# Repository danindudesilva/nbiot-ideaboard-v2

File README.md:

# Ideamart NB-IoT Ideaboard
###### version 2.0

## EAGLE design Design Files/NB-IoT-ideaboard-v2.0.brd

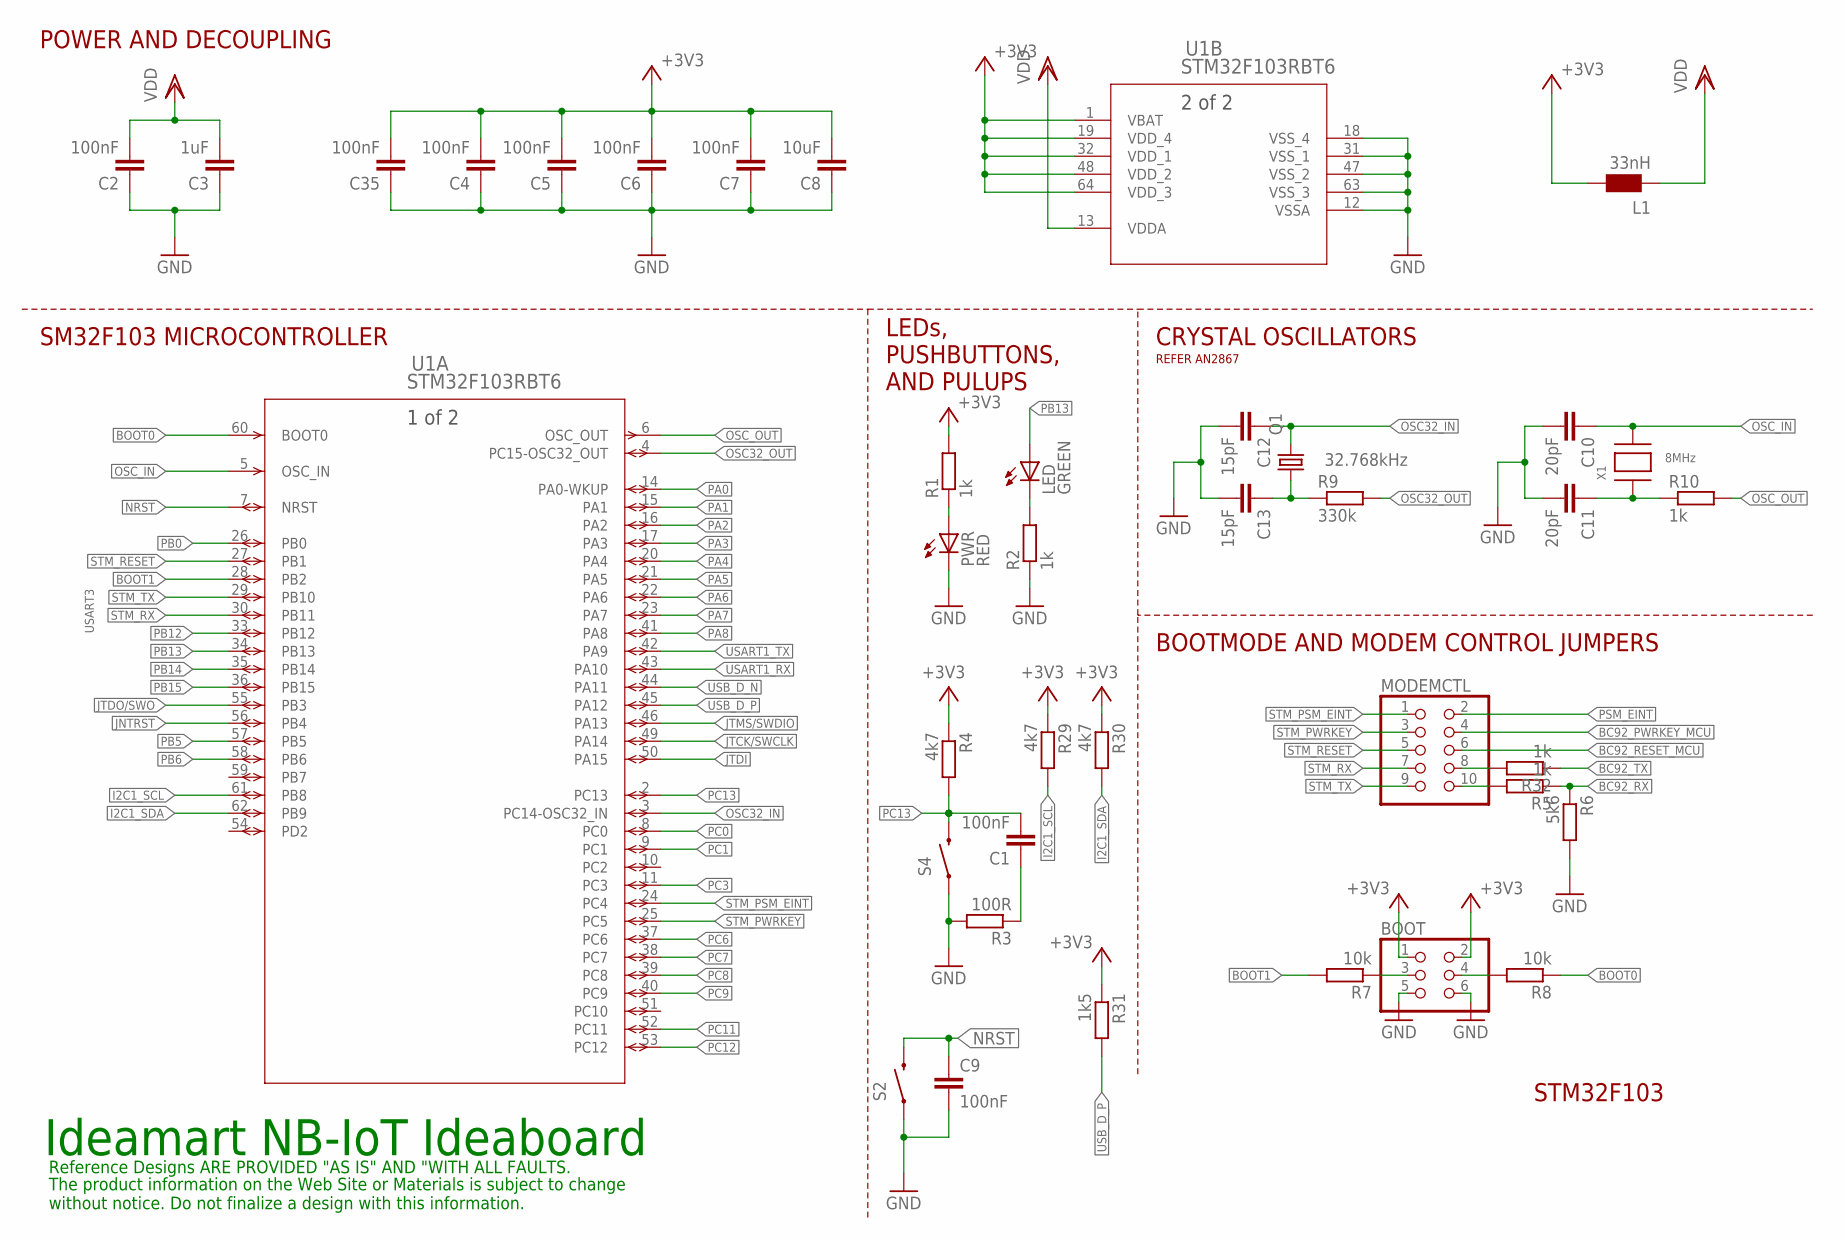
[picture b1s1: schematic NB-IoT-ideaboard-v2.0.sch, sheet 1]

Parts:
BOOT: PINHD-2X03_2.54; 2X03
C1, C2, C4, C5, C6, C7, C9, C35: 100nF; C0805
C3: 1uF; C0805
C8: 10uF; C1206
C10, C11: 20pF; C0805
C12, C13: 15pF; C0805
L1: 33nH; 0603
LED: GREEN; CHIP-LED0805
MODEMCTL: PINHD-2X05_2.54; 2X05
PWR: RED; CHIP-LED0805
Q1: 32.768kHz; 3.2X1.5
R1, R2, R5, R10, R32: 1k; R0805
R3: 100R; R0805
R4, R29, R30: 4k7; R0805
R6: 5k6; R0805
R7, R8: 10k; R0805
R9: 330k; R0805
R31: 1k5; R0805
S2, S4: SWITCH-MOMENTARY-2SMD; TACTILE-SWITCH-SMD
U1: STM32F103RBT6; LQFP64-10X10MM
X1: 8MHz; NX5032

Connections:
+3V3: BOOT.1, BOOT.2, C4.2, C5.2, C6.2, C7.2, C8.2, C35.2, L1.2, R1.2, R4.1, R29.1, R30.1, R31.1, U1.1 (VBAT), U1.19 (VDD_4), U1.32 (VDD_1), U1.48 (VDD_2), U1.64 (VDD_3); also elsewhere on the board
BC92_PWRKEY_MCU: MODEMCTL.4; also elsewhere on the board
BC92_RESET_MCU: MODEMCTL.6; also elsewhere on the board
BC92_RX: R5.1, R6.1; also elsewhere on the board
BC92_TX: R32.1; also elsewhere on the board
BOOT0: R8.1, U1.60 (BOOT0)
BOOT1: R7.2, U1.28 (PB2)
GND: BOOT.5, BOOT.6, C2.1, C3.1, C4.1, C5.1, C6.1, C7.1, C8.1, C9.2, C10.2, C11.2, C12.2, C13.2, C35.1, PWR.C, R2.1, R3.2, R6.2, S2.1, S4.1, U1.12 (VSSA), U1.18 (VSS_4), U1.31 (VSS_1), U1.47 (VSS_2), U1.63 (VSS_3); also elsewhere on the board
I2C1_SCL: R29.2, U1.61 (PB8); also elsewhere on the board
I2C1_SDA: R30.2, U1.62 (PB9); also elsewhere on the board
JNTRST: U1.56 (PB4); also elsewhere on the board
JTCK/SWCLK: U1.49 (PA14); also elsewhere on the board
JTDI: U1.50 (PA15)
JTDO/SWO: U1.55 (PB3); also elsewhere on the board
JTMS/SWDIO: U1.46 (PA13); also elsewhere on the board
unnamed: BOOT.3, R7.1
unnamed: PWR.A, R1.1
unnamed: C11.1, R10.1, X1.P$1
unnamed: C13.1, Q1.1, R9.1
unnamed: MODEMCTL.10, R5.2
unnamed: MODEMCTL.8, R32.2
unnamed: C1.1, R3.1
unnamed: BOOT.4, R8.2
unnamed: LED.C, R2.2
NRST: C9.1, S2.3 (2), U1.7 (NRST); also elsewhere on the board
OSC32_IN: C12.1, Q1.2, U1.3 (PC14-OSC32_IN)
OSC32_OUT: R9.2, U1.4 (PC15-OSC32_OUT)
OSC_IN: C10.1, U1.5 (OSC_IN), X1.P$2
OSC_OUT: R10.2, U1.6 (OSC_OUT)
PA0: U1.14 (PA0-WKUP); also elsewhere on the board
PA1: U1.15 (PA1); also elsewhere on the board
PA2: U1.16 (PA2); also elsewhere on the board
PA3: U1.17 (PA3); also elsewhere on the board
PA4: U1.20 (PA4); also elsewhere on the board
PA5: U1.21 (PA5); also elsewhere on the board
PA6: U1.22 (PA6); also elsewhere on the board
PA7: U1.23 (PA7); also elsewhere on the board
PA8: U1.41 (PA8); also elsewhere on the board
PB0: U1.26 (PB0); also elsewhere on the board
PB5: U1.57 (PB5); also elsewhere on the board
PB6: U1.58 (PB6); also elsewhere on the board
PB12: U1.33 (PB12); also elsewhere on the board
PB13: LED.A, U1.34 (PB13); also elsewhere on the board
PB14: U1.35 (PB14); also elsewhere on the board
PB15: U1.36 (PB15); also elsewhere on the board
PC0: U1.8 (PC0); also elsewhere on the board
PC1: U1.9 (PC1); also elsewhere on the board
PC3: U1.11 (PC3); also elsewhere on the board
PC6: U1.37 (PC6); also elsewhere on the board
PC7: U1.38 (PC7); also elsewhere on the board
PC8: U1.39 (PC8); also elsewhere on the board
PC9: U1.40 (PC9); also elsewhere on the board
PC11: U1.52 (PC11); also elsewhere on the board
PC12: U1.53 (PC12); also elsewhere on the board
PC13: C1.2, R4.2, S4.3 (2), U1.2 (PC13)
PSM_EINT: MODEMCTL.2; also elsewhere on the board
STM_PSM_EINT: MODEMCTL.1, U1.24 (PC4)
STM_PWRKEY: MODEMCTL.3, U1.25 (PC5)
STM_RESET: MODEMCTL.5, U1.27 (PB1)
STM_RX: MODEMCTL.7, U1.30 (PB11)
STM_TX: MODEMCTL.9, U1.29 (PB10)
USART1_RX: U1.43 (PA10); also elsewhere on the board
USART1_TX: U1.42 (PA9); also elsewhere on the board
USB_D_N: U1.44 (PA11); also elsewhere on the board
USB_D_P: R31.2, U1.45 (PA12); also elsewhere on the board
VDD: C2.2, C3.2, L1.1, U1.13 (VDDA)

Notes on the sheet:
Ideamart NB-IoT Ideaboard
Reference Designs ARE PROVIDED "AS IS" AND "WITH ALL FAULTS.
The product information on the Web Site or Materials is subject to change without notice. Do not finalize a design with this information.
USART3
POWER AND DECOUPLING
SM32F103 MICROCONTROLLER
BOOTMODE AND MODEM CONTROL JUMPERS
CRYSTAL OSCILLATORS
LEDs, PUSHBUTTONS, AND PULUPS
STM32F103
REFER AN2867

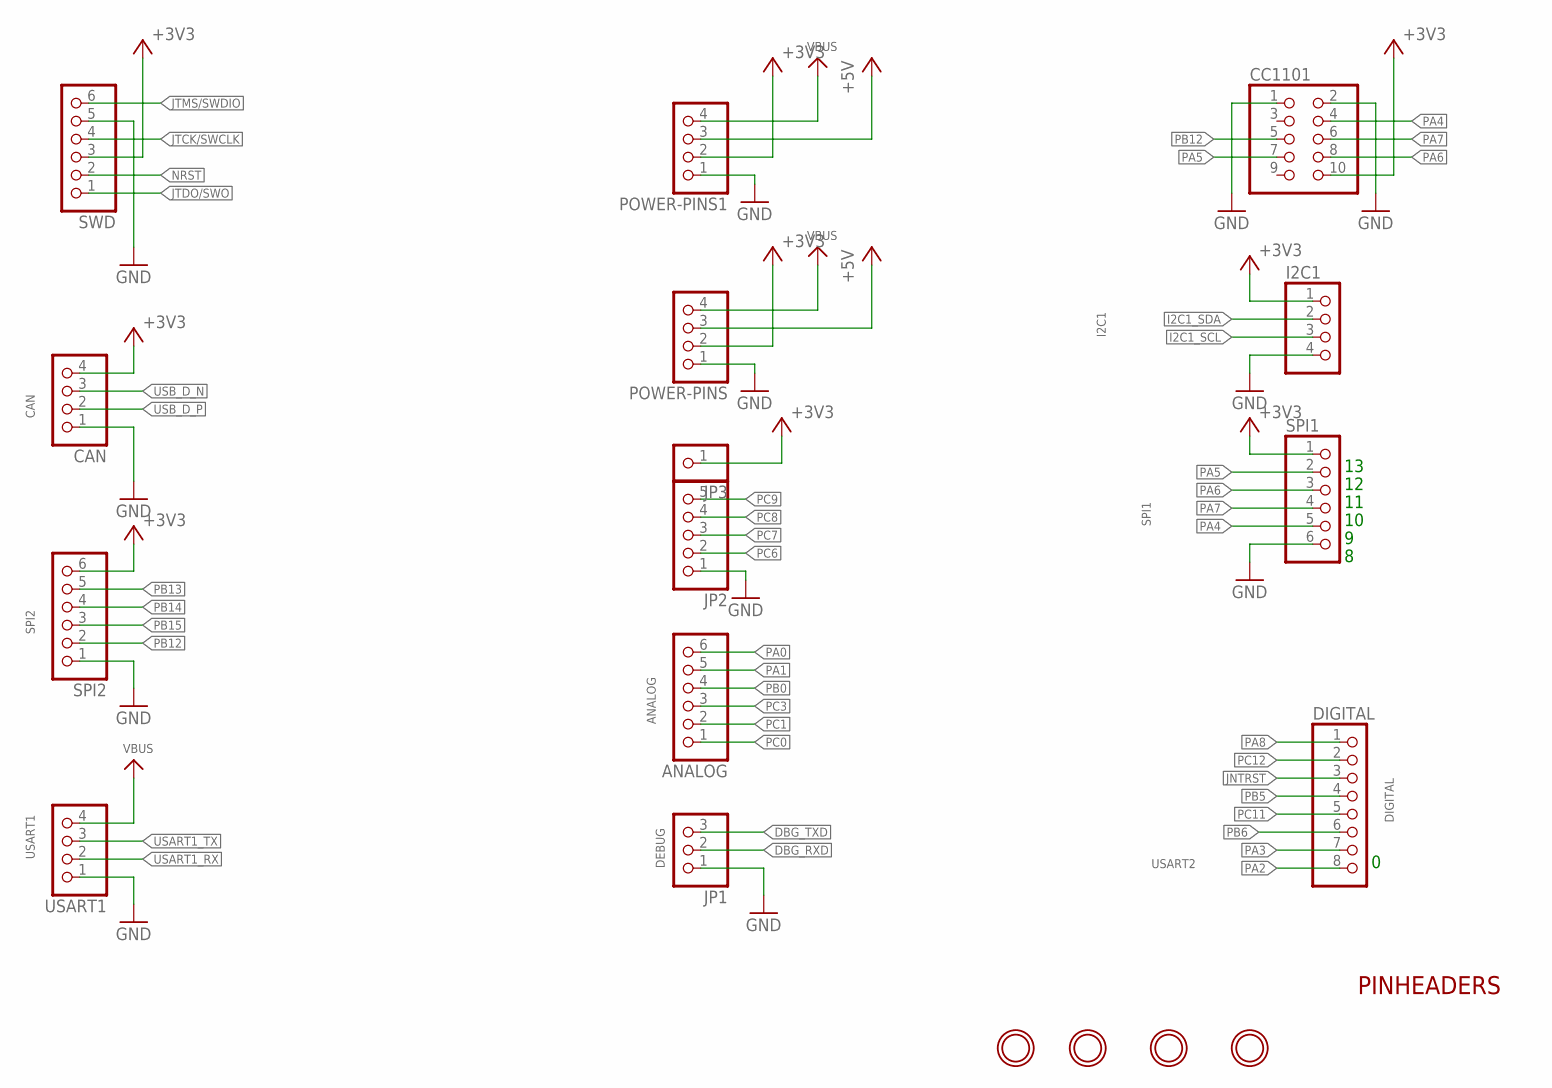
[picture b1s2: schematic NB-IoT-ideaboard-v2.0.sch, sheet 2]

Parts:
$H1, $H2, $H3, $H4: MOUNTINGHOLE3.0THIN; MOUNTINGHOLE_3.0_PLATEDTHIN
ANALOG: PINHD-1X06_2.54-S; 1X06-S
CAN: PINHD-1X04_2.54-S; 1X04-S
CC1101: PINHD-2X05_2.54; 2X05
DIGITAL: PINHD-1X08_2.54-S; 1X08-S
I2C1: PINHD-1X04_2.54-S; 1X04-S
JP1: PINHD-1X03_2.54-S; 1X03-S
JP2: PINHD-1X05_2.54-S; 1X05-S
JP3: PINHD-1X01_2.54-S; 1X01-S
POWER-PINS, POWER-PINS1: PINHD-1X04_2.54-S; 1X04-S
SPI1, SPI2: PINHD-1X06_2.54-S; 1X06-S
SWD: PINHD-1X06_2.54-S; 1X06-S
USART1: PINHD-1X04_2.54-S; 1X04-S

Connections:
+3V3: CAN.4, CC1101.10, I2C1.1, JP3.1, POWER-PINS.2, POWER-PINS1.2, SPI1.1, SPI2.6, SWD.3; also elsewhere on the board
+5V: POWER-PINS.3, POWER-PINS1.3; also elsewhere on the board
DBG_RXD: JP1.2; also elsewhere on the board
DBG_TXD: JP1.3; also elsewhere on the board
GND: CAN.1, CC1101.1, CC1101.2, I2C1.4, JP1.1, JP2.1, POWER-PINS.1, POWER-PINS1.1, SPI1.6, SPI2.1, SWD.5, USART1.1; also elsewhere on the board
I2C1_SCL: I2C1.3; also elsewhere on the board
I2C1_SDA: I2C1.2; also elsewhere on the board
JNTRST: DIGITAL.3; also elsewhere on the board
JTCK/SWCLK: SWD.4; also elsewhere on the board
JTDO/SWO: SWD.1; also elsewhere on the board
JTMS/SWDIO: SWD.6; also elsewhere on the board
NRST: SWD.2; also elsewhere on the board
PA0: ANALOG.6; also elsewhere on the board
PA1: ANALOG.5; also elsewhere on the board
PA2: DIGITAL.8; also elsewhere on the board
PA3: DIGITAL.7; also elsewhere on the board
PA4: CC1101.4, SPI1.5; also elsewhere on the board
PA5: CC1101.7, SPI1.2; also elsewhere on the board
PA6: CC1101.8, SPI1.3; also elsewhere on the board
PA7: CC1101.6, SPI1.4; also elsewhere on the board
PA8: DIGITAL.1; also elsewhere on the board
PB0: ANALOG.4; also elsewhere on the board
PB5: DIGITAL.4; also elsewhere on the board
PB6: DIGITAL.6; also elsewhere on the board
PB12: CC1101.5, SPI2.2; also elsewhere on the board
PB13: SPI2.5; also elsewhere on the board
PB14: SPI2.4; also elsewhere on the board
PB15: SPI2.3; also elsewhere on the board
PC0: ANALOG.1; also elsewhere on the board
PC1: ANALOG.2; also elsewhere on the board
PC3: ANALOG.3; also elsewhere on the board
PC6: JP2.2; also elsewhere on the board
PC7: JP2.3; also elsewhere on the board
PC8: JP2.4; also elsewhere on the board
PC9: JP2.5; also elsewhere on the board
PC11: DIGITAL.5; also elsewhere on the board
PC12: DIGITAL.2; also elsewhere on the board
USART1_RX: USART1.2; also elsewhere on the board
USART1_TX: USART1.3; also elsewhere on the board
USB_D_N: CAN.3; also elsewhere on the board
USB_D_P: CAN.2; also elsewhere on the board
VBUS: POWER-PINS.4, POWER-PINS1.4, USART1.4; also elsewhere on the board

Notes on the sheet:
I2C1
SPI1
USART2
CAN
SPI2
USART1
ANALOG
DEBUG
DIGITAL
PINHEADERS

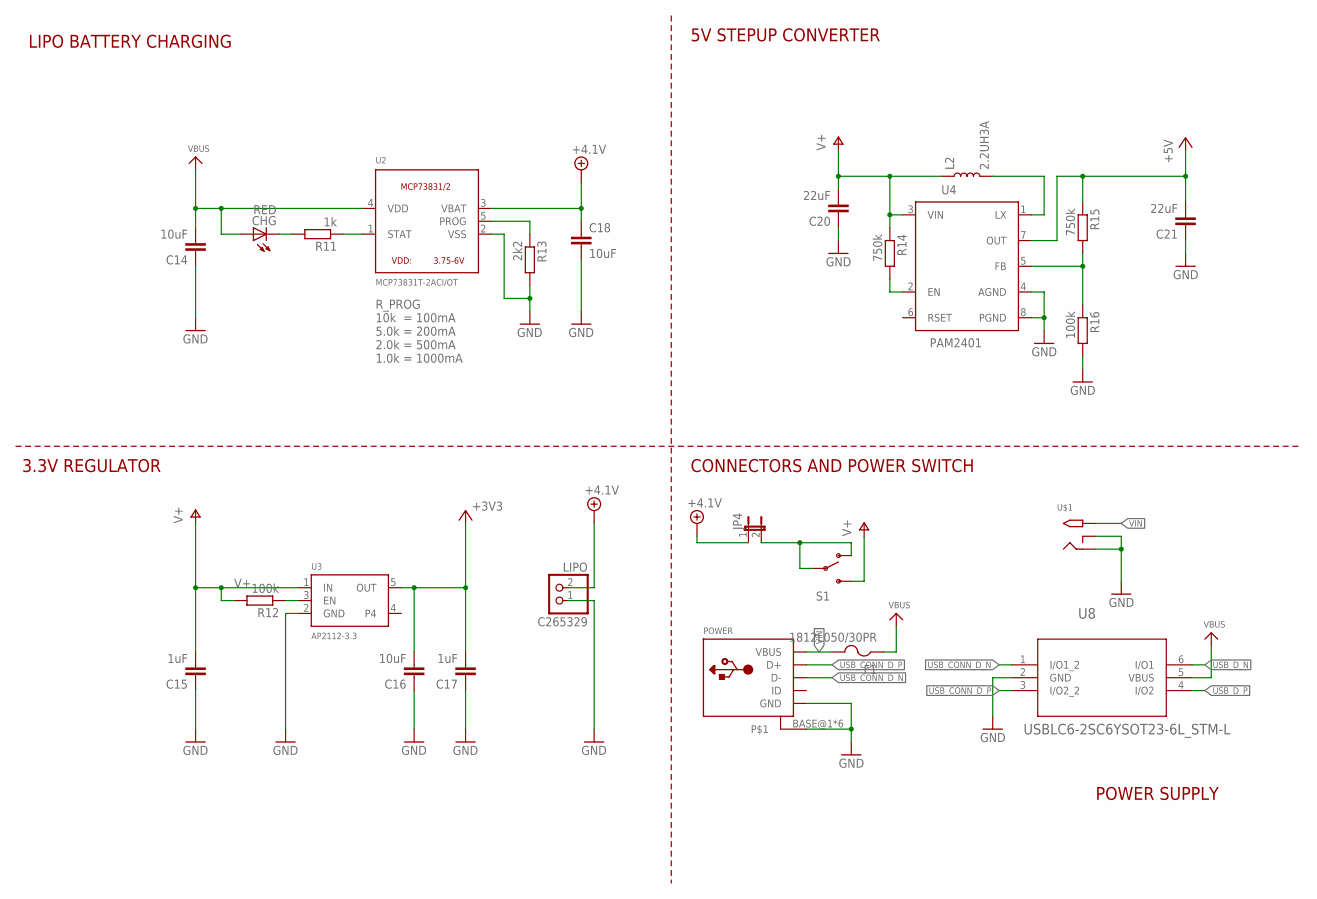
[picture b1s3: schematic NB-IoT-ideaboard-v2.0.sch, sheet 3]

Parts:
C14, C16, C18: 10uF; C0805
C15, C17: 1uF; C0805
C20, C21: 22uF; C0805
CHG: RED; CHIP-LED0805
F1: 1812L050/30PR; 1812
JP4: JP1E; JP1
L2: 2.2UH3A; INDUCTOR_4X4MM
LIPO: C265329; JST-PH-2-SMT
POWER: USB_MICRO_20329_V2; 4UCONN_20329_V2
R11: 1k; R0805
R12, R16: 100k; R0805
R13: 2k2; R0805
R14, R15: 750k; R0805
S1: SWITCH-SPDT-SMD-A; SWITCH-SPST-SMD-A
U2: MCP73831T-2ACI/OT; SOT23-5
U3: AP2112-3.3; SOT23-5
U4: PAM2401; MSOP8
U8: USBLC6-2SC6YSOT23-6L_STM-L; SOT23-6L_STM-L
U$1: 2.1MMJACKSMT; DCJACK_2MM_SMT

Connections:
+3V3: C16.2, C17.2, U3.5 (OUT); also elsewhere on the board
+4.1V: C18.1, JP4.1, LIPO.2 (1), U2.3 (VBAT)
+5V: C21.2, R15.1, U4.7 (OUT); also elsewhere on the board
EN: R14.2, U4.2 (EN)
GND: C14.1, C15.1, C16.1, C17.1, C18.2, C20.1, C21.1, LIPO.1 (2), POWER.BASE@1, POWER.BASE@2, POWER.GND, POWER.SPRT@1, POWER.SPRT@2, POWER.SPRT@3, POWER.SPRT@4, R13.2, R16.2, U2.2 (VSS), U3.2 (GND), U4.4 (AGND), U4.8 (PGND), U8.2 (GND), U$1.GND (RING), U$1.GNDBREAK (RING_SW); also elsewhere on the board
unnamed: R12.1, U3.3 (EN)
unnamed: CHG.C, R11.2
unnamed: R11.1, U2.1 (STAT)
unnamed: R13.1, U2.5 (PROG)
unnamed: R15.2, R16.1, U4.5 (FB)
unnamed: L2.P$2 (2), U4.1 (LX)
unnamed: JP4.2, S1.1 (O), S1.2
USB_CONN_D_N: POWER.D-, U8.1 (I/O1_2)
USB_CONN_D_P: POWER.D+, U8.3 (I/O2_2)
USB_D_N: U8.6 (I/O1); also elsewhere on the board
USB_D_P: U8.4 (I/O2); also elsewhere on the board
V+: C15.2, C20.2, L2.P$1 (1), R12.2, R14.1, S1.3 (S), U3.1 (IN), U4.3 (VIN); also elsewhere on the board
VBUS: C14.2, CHG.A, F1.1, U2.4 (VDD), U8.5 (VBUS); also elsewhere on the board
VIN: F1.2, POWER.VBUS, U$1.PWR2 (TIP)

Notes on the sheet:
R_PROG 10k = 100mA 5.0k = 200mA 2.0k = 500mA 1.0k = 1000mA
LIPO BATTERY CHARGING
5V STEPUP CONVERTER
3.3V REGULATOR
CONNECTORS AND POWER SWITCH
POWER SUPPLY

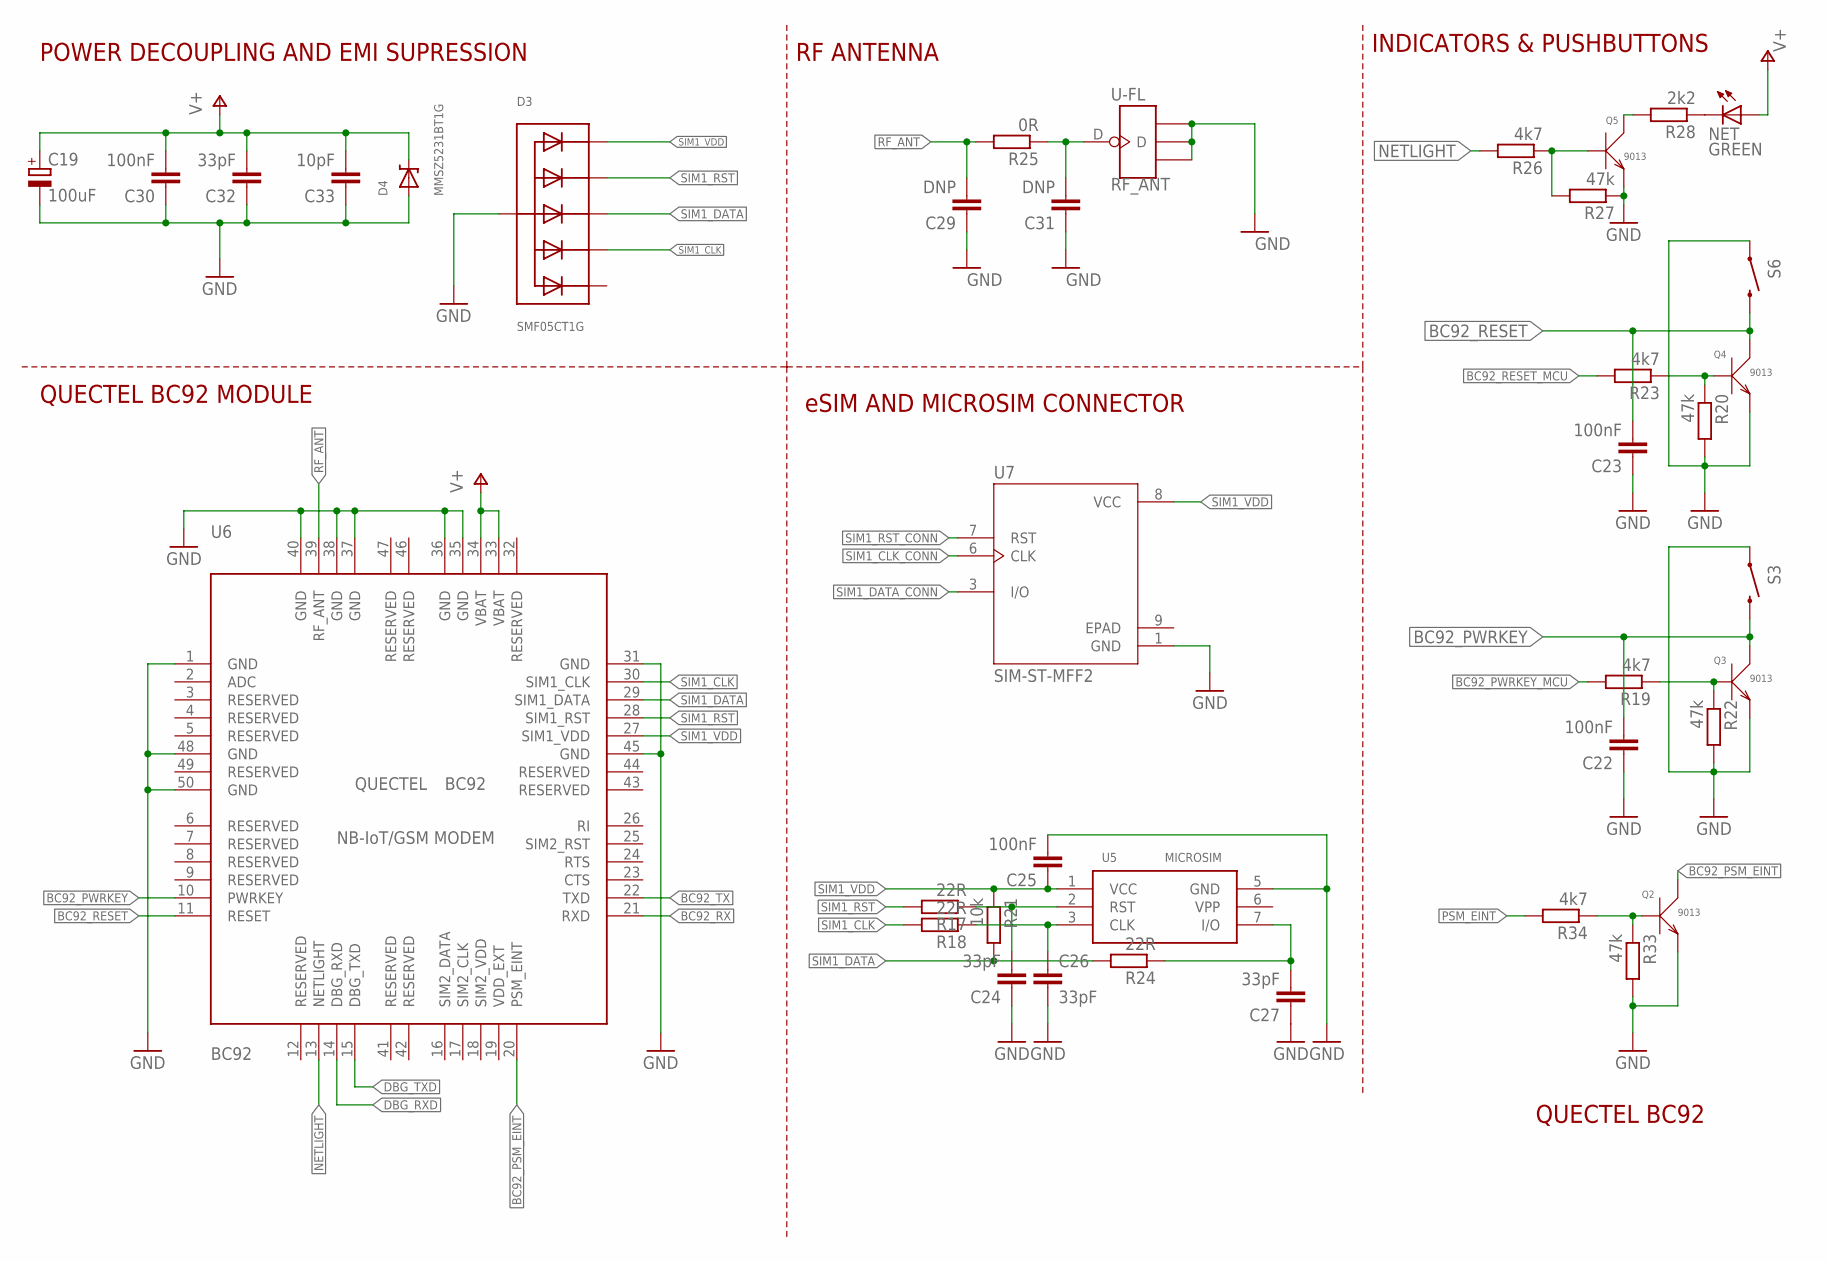
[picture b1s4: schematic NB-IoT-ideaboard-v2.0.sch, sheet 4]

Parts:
C19: 100uF; B/3528-21R
C22, C23, C25, C30: 100nF; C0805
C24, C26, C27, C32: 33pF; C0805
C29, C31: DNP; C0805
C33: 10pF; C0805
D3: SMF05CT1G; SOT363
D4: MMSZ5231BT1G; SOD-123
NET: GREEN; CHIP-LED0805
Q2, Q3, Q4, Q5: 9013; SOT23
R17, R18, R24: 22R; R0805
R19, R23, R26, R34: 4k7; R0805
R20, R22, R27, R33: 47k; R0805
R21: 10k; R0805
R25: 0R; R0805
R28: 2k2; R0805
RF_ANT: U-FL; 4P-U-FL
S3, S6: SWITCH-MOMENTARY-2SMD; TACTILE-SWITCH-SMD
U5: MICROSIM
U6: BC92
U7: SIM-ST-MFF2; PSON127P500X600X82-9N

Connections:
BC92_PSM_EINT: Q2.3 (C), U6.20 (PSM_EINT)
BC92_PWRKEY: C22.2, Q3.3 (C), S3.3 (2), U6.10 (PWRKEY)
BC92_PWRKEY_MCU: R19.2; also elsewhere on the board
BC92_RESET: C23.2, Q4.3 (C), S6.3 (2), U6.11 (RESET)
BC92_RESET_MCU: R23.2; also elsewhere on the board
BC92_RX: U6.21 (RXD); also elsewhere on the board
BC92_TX: U6.22 (TXD); also elsewhere on the board
DBG_RXD: U6.14 (DBG_RXD); also elsewhere on the board
DBG_TXD: U6.15 (DBG_TXD); also elsewhere on the board
GND: C19.-, C22.1, C23.1, C24.1, C25.2, C26.2, C27.1, C29.1, C30.1, C31.1, C32.1, C33.1, D3.2 (A), D4.A, Q2.2 (E), Q3.2 (E), Q4.2 (E), Q5.2 (E), R20.2, R22.2, R27.1, R33.2, RF_ANT.GND1, RF_ANT.GND2, RF_ANT.GND3, S3.1, S6.1, U5.5 (GND), U6.1 (GND), U6.31 (GND), U6.35 (GND), U6.36 (GND), U6.37 (GND), U6.38 (GND), U6.40 (GND), U6.45 (GND), U6.48 (GND), U6.50 (GND), U7.1 (GND); also elsewhere on the board
unnamed: Q3.1 (B), R19.1, R22.1
unnamed: Q4.1 (B), R20.1, R23.1
unnamed: C31.2, R25.1, RF_ANT.D
unnamed: NET.C, R28.1
unnamed: Q5.3 (C), R28.2
unnamed: Q5.1 (B), R26.1, R27.2
unnamed: Q2.1 (B), R33.1, R34.1
NETLIGHT: R26.2, U6.13 (NETLIGHT)
PSM_EINT: R34.2; also elsewhere on the board
RF_ANT: C29.2, R25.2, U6.39 (RF_ANT)
SIM1_CLK: D3.5 (C4), R18.2, U6.30 (SIM1_CLK)
SIM1_CLK_CONN: C26.1, R18.1, U5.3 (CLK), U7.6 (CLK)
SIM1_DATA: D3.4 (C3), R21.2, R24.2, U6.29 (SIM1_DATA)
SIM1_DATA_CONN: C27.2, R24.1, U5.7 (I/O), U7.3 (I/O)
SIM1_RST: D3.3 (C2), R17.2, U6.28 (SIM1_RST)
SIM1_RST_CONN: C24.2, R17.1, U5.2 (RST), U7.7 (RST)
SIM1_VDD: C25.1, D3.1 (C1), R21.1, U5.1 (VCC), U6.27 (SIM1_VDD), U7.8 (VCC)
V+: C19.+, C30.2, C32.2, C33.2, D4.C, NET.A, U6.33 (VBAT), U6.34 (VBAT); also elsewhere on the board

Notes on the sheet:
QUECTEL BC92
POWER DECOUPLING AND EMI SUPRESSION
RF ANTENNA
INDICATORS & PUSHBUTTONS
eSIM AND MICROSIM CONNECTOR
QUECTEL BC92 MODULE

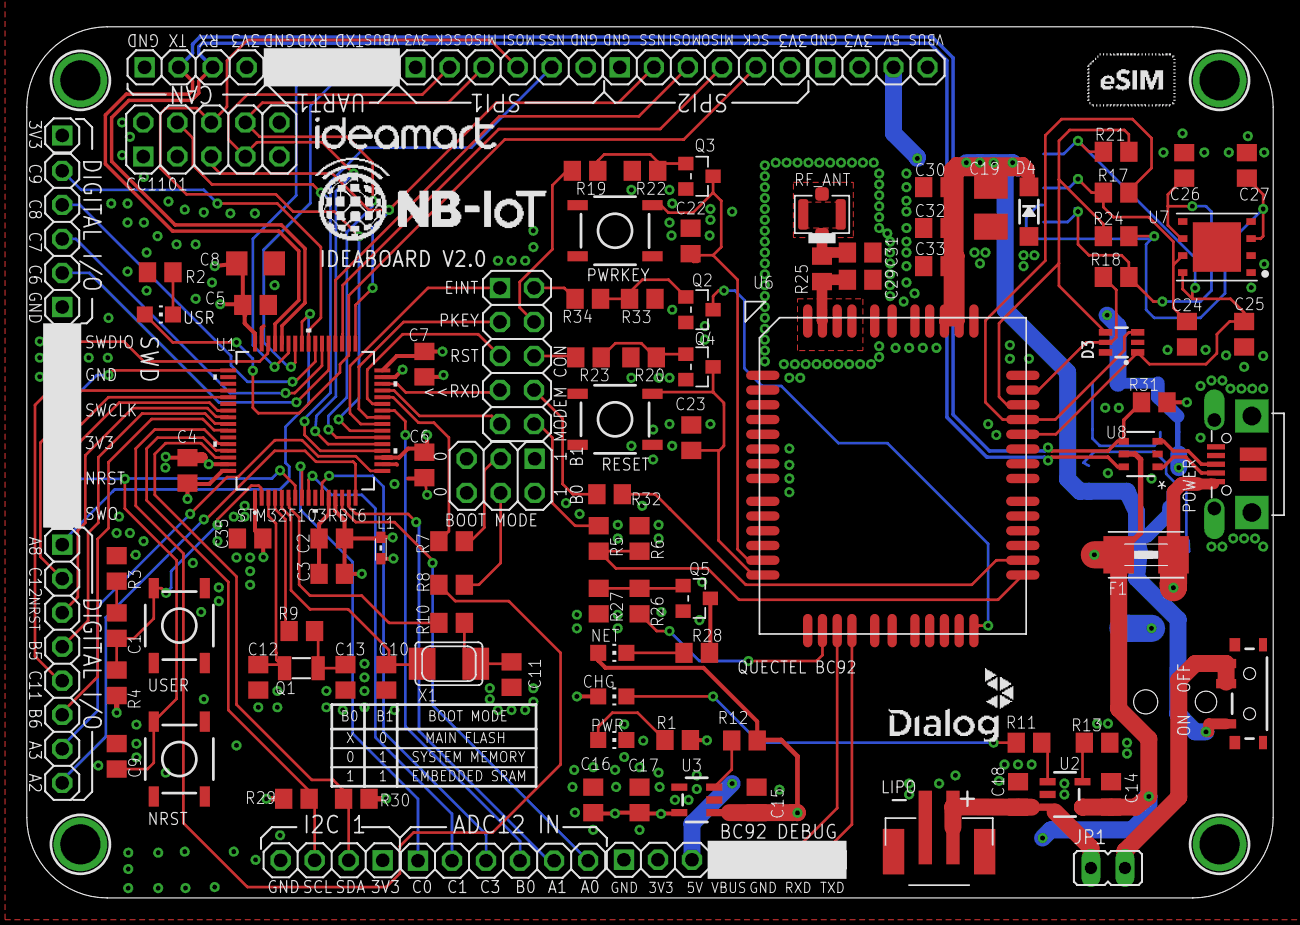
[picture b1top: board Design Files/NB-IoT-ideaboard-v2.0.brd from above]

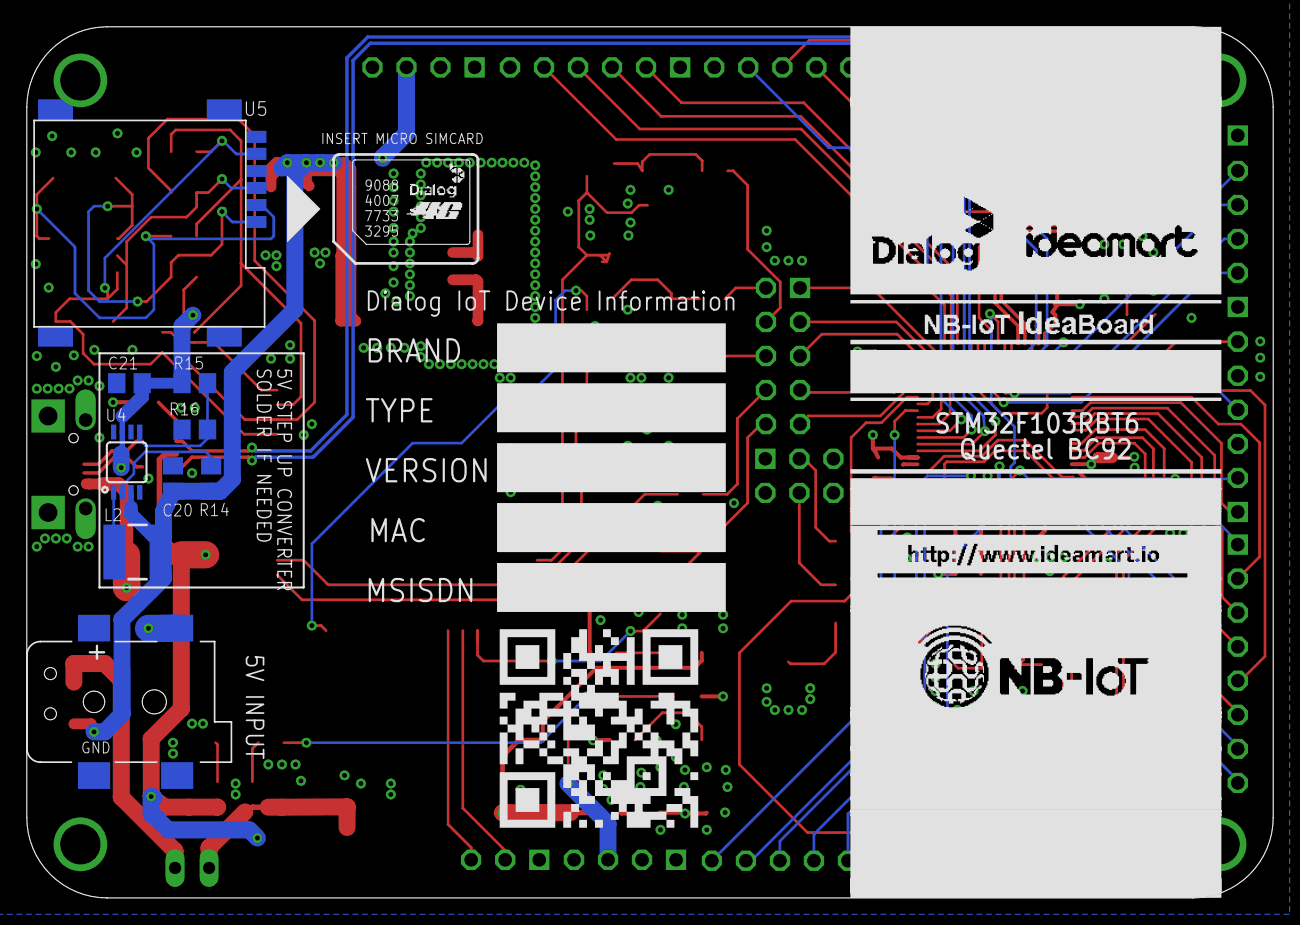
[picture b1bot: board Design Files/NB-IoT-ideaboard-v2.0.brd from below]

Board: 4 copper layers, 93.0 x 65.0 mm, 120 parts (9 on the bottom side), 101 nets.

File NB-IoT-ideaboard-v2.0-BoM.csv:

"Qty";"Value";"Device";"Package";"Parts";"Description";"BOM";"BUILT_BY";"COPYRIGHT";"MANUFACTURER_PART_NUMBER";"MF";"MPN";"OC_FARNELL";"OC_NEWARK";"PROD_ID";"SOURCELIBRARY";"VALUE";"VENDOR";
"1";"";"JST_2PIN-SMT";"JST-PH-2-SMT";"LIPO";"JST 2-Pin Connectors of various flavors";"";"";"";"";"";"";"";"";"";"";"";"";
"1";"";"PINHD-1X10";"1X10";"JP6";"PIN HEADER";"";"";"";"";"";"";"";"";"";"";"";"";
"1";"";"PINHD-1X10_2.54-S";"1X10-S";"JP9";"PIN HEADER";"";"";"";"";"";"";"";"";"";"";"";"";
"3";"";"PINHD-1X6";"1X06";"JP4, JP5, SWD";"PIN HEADER";"";"";"";"";"";"";"";"";"";"";"";"";
"1";"";"PINHD-1X8";"1X08";"JP7";"PIN HEADER";"";"";"";"";"";"";"";"";"";"";"";"";
"1";"";"PINHD-2X03_2.54-SMD";"2X03SMD";"BOOT";"PIN HEADER";"";"";"";"";"";"";"";"";"";"";"";"";
"2";"";"PINHD-2X05_2.54-SMD";"2X05SMD";"CC1101, MODEMCTL";"PIN HEADER";"";"";"";"";"";"";"";"";"";"";"";"";
"1";"";"SWITCH-SPDTSMD2";"SWITCH-SPDT-SMD";"S1";"SPDT Switch";"";"";"";"";"";"";"";"";"";"";"";"";
"1";"";"TVSARRAY_5LANE";"SOT363";"D3";"Voltage Transient Suppressor Array";"";"";"";"";"";"";"";"";"";"";"";"";
"1";"";"USB_MICRO_20329_V2";"4UCONN_20329_V2";"POWER";"USB Connectors";"";"";"";"";"";"";"";"";"";"";"";"";
"1";"100R";"R-US_M0805";"M0805";"R3";"RESISTOR, American symbol";"";"";"";"";"";"";"";"";"";"";"";"";
"2";"100k";"R-US_M0805";"M0805";"R12, R16";"RESISTOR, American symbol";"";"";"";"";"";"";"";"";"";"";"";"";
"1";"100n";"CAP_CERAMIC_0805MP";"_0805MP";"C19";"Ceramic Capacitors";"";"";"";"";"";"";"";"";"";"";"";"";
"6";"100nF";"CAP_CERAMIC_0805";"_0805";"C22, C23, C25, C29, C30, C31";"Ceramic Capacitors";"";"";"";"";"";"";"";"";"";"";"";"";
"7";"100nF";"CAP_CERAMIC_0805MP";"_0805MP";"C1, C2, C4, C5, C6, C7, C9";"Ceramic Capacitors";"";"";"";"";"";"";"";"";"";"";"";"";
"1";"100uF";"C-USC1210";"C1210";"C28";"CAPACITOR, American symbol";"";"";"";"";"";"";"";"";"";"";"";"";
"1";"10k";"R-0805";"0805";"R21";"";"";"";"";"";"";"";"";"";"";"";"";"";
"2";"10k";"R-US_M0805";"M0805";"R7, R8";"RESISTOR, American symbol";"";"";"";"";"";"";"";"";"";"";"";"";
"1";"10pF";"CAP_CERAMIC_0805";"_0805";"C33";"Ceramic Capacitors";"";"";"";"";"";"";"";"";"";"";"";"";
"2";"10uF";"CAP_CERAMIC_0805";"_0805";"C14, C18";"Ceramic Capacitors";"";"";"";"";"";"";"";"";"";"";"";"";
"3";"10uF";"CAP_CERAMIC_0805MP";"_0805MP";"C8, C15, C16";"Ceramic Capacitors";"";"";"";"";"";"";"";"";"";"";"";"";
"1";"1M";"R-US_M0805";"M0805";"R9";"RESISTOR, American symbol";"";"";"";"";"";"";"";"";"";"";"";"";
"1";"1k";"R-EU_R0805";"R0805";"R1";"RESISTOR, European symbol";"";"";"";"";"";"";"";"";"";"";"";"";
"3";"1k";"R-US_M0805";"M0805";"R5, R10, R11";"RESISTOR, American symbol";"";"";"";"";"";"";"";"";"";"";"";"";
"2";"1uF";"CAP_CERAMIC_0805MP";"_0805MP";"C3, C17";"Ceramic Capacitors";"";"";"";"";"";"";"";"";"";"";"";"";
"1";"2.1MMJACKSMT";"2.1MMJACKSMT";"DCJACK_2MM_SMT";"U$1";"2.1mm x 5.5mm THM DC jack with internal switch. Digikey part #PJ-102A, 4UCON part #05537";"";"";"";"";"";"";"";"";"";"";"";"";
"1";"2.2UH3A";"INDUCTOR-IFSC1515AHER2R2M01";"INDUCTOR_4X4MM";"L2";"Inductors";"";"";"";"";"";"";"";"";"NDUC-13770";"";"2.2UH3A";"";
"2";"2.2k";"R-0805";"0805";"R25, R28";"";"";"";"";"";"";"";"";"";"";"";"";"";
"1";"2.2k";"R-US_M0805";"M0805";"R13";"RESISTOR, American symbol";"";"";"";"";"";"";"";"";"";"";"";"";
"2";"20pF";"CAP_CERAMIC_0805MP";"_0805MP";"C10, C11";"Ceramic Capacitors";"";"";"";"";"";"";"";"";"";"";"";"";
"3";"22R";"R-0805";"0805";"R17, R18, R24";"";"";"";"";"";"";"";"";"";"";"";"";"";
"2";"22uF";"22UF-0805-6.3V-20%";"0805";"C20, C21";"22µF ceramic capacitors";"";"";"";"";"";"";"";"";"CAP-08402";"";"22uF";"";
"1";"32.768kHz";"CRYSTALTC26H-SMD";"TC26H-SMD";"Q1";"CRYSTAL";"";"";"";"";"";"";"";"";"";"";"";"";
"1";"330R";"R-US_M0805";"M0805";"R2";"RESISTOR, American symbol";"";"";"";"";"";"";"";"";"";"";"";"";
"4";"33pF";"CAP_CERAMIC_0805";"_0805";"C24, C26, C27, C32";"Ceramic Capacitors";"";"";"";"";"";"";"";"";"";"";"";"";
"2";"4.3pF";"CAP_CERAMIC_0805MP";"_0805MP";"C12, C13";"Ceramic Capacitors";"";"";"";"";"";"";"";"";"";"";"";"";
"3";"4.7k";"R-0805";"0805";"R19, R20, R26";"";"";"";"";"";"";"";"";"";"";"";"";"";
"3";"47k";"R-0805";"0805";"R22, R23, R27";"";"";"";"";"";"";"";"";"";"";"";"";"";
"1";"4k7";"R-US_M0805";"M0805";"R4";"RESISTOR, American symbol";"";"";"";"";"";"";"";"";"";"";"";"";
"1";"5.6k";"R-US_M0805";"M0805";"R6";"RESISTOR, American symbol";"";"";"";"";"";"";"";"";"";"";"";"";
"2";"750k";"R-US_M0805";"M0805";"R14, R15";"RESISTOR, American symbol";"";"";"";"";"";"";"";"";"";"";"";"";
"1";"8MHz";"CRYSTALSM49";"SM49";"Q2";"CRYSTAL";"";"";"";"";"";"";"unknown";"unknown";"";"";"";"";
"3";"9013";"TRANSISTOR-NPN-SOT23";"SOT23";"Q3, Q4, Q5";"NPN audion";"";"";"";"";"";"";"";"";"";"";"";"";
"1";"AP2112-3.3";"VREG_SOT23-5";"SOT23-5";"U3";"SOT23-5 Fixed Voltage Regulators";"";"";"";"";"";"";"";"";"";"";"";"";
"1";"BC92";"BC92";"BC92";"U6";"";"";"";"";"";"";"";"";"";"";"";"";"";
"1";"BLM21BB201SN1D";"WE-CBF_0805";"0805";"L1";"SMD EMI Suppression Ferrite Beads";"";"";"";"";"";"";"";"";"";"";"";"";
"1";"GREEN";"LEDCHIP-LED0805";"CHIP-LED0805";"PWR";"LED";"";"";"";"";"";"";"";"";"";"";"";"";
"4";"KSS-2EG4430";"KSS-2EG4430";"KSS-2EG4430";"NRST, PWRKEY, RESET, USER";"Size: 3x6mm";"";"";"";"";"";"";"";"";"";"";"";"";
"1";"MCP73831T-2ACI/OT";"MCP73831/2";"SOT23-5";"U2";"MCP73831/2 LIPO Charger";"";"";"";"";"";"";"";"";"";"";"";"";
"1";"MICROSIM";"MICROSIM";"MICROSIM";"U5";"";"";"";"";"";"";"";"";"";"";"";"";"";
"1";"MMSZ5231BT1G";"DIODE-ZENERSOD123";"SOD-123";"D4";"Zener Diode";"";"";"";"";"";"";"";"";"";"";"";"";
"3";"MOUNTINGHOLE3.0THIN";"MOUNTINGHOLE3.0THIN";"MOUNTINGHOLE_3.0_PLATEDTHIN";"$H1, $H2, $H3";"Mounting Hole";"EXCLUDE";"";"";"";"";"";"";"";"";"";"";"";
"2";"ORANGE";"LED0805";"CHIPLED_0805";"CHG, LED";"LED";"";"";"";"";"";"";"";"";"";"";"";"";
"1";"PAM2401";"PAM2401";"MSOP8";"U4";"PAM2401 - Boost PMIC";"";"";"";"";"";"";"";"";"IC-13769";"";"PAM2401";"";
"1";"RED";"LED'0805'";"LED-0805";"NET";"";"";"";"";"";"";"";"";"";"";"";"";"";
"1";"STM32F103RBT6";"STM32F103RBT6";"LQFP64-10X10MM";"U1";"";"";"EMA_UL_Team";"Copyright (C) 2018 Accelerated Designs. All rights reserved";"STM32F103RBT6";"";"";"";"";"";"Updates_to_database_2020-10-19";"";"STMicroelectronics";
"1";"U-FL";"ANTENNA-U-FL";"4P-U-FL";"ANT1";"";"";"";"";"";"";"";"";"";"";"";"";"";

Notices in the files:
parts and their libraries:
SparkFun-Coils: Licensing: Creative Commons ShareAlike 4.0 International - https://creativecommons.org/licenses/by-sa/4.0
crystal-geyer_V1_0: Copyright: Geyer-Electronic
COPYRIGHT: Copyright (C) 2018 Accelerated Designs. All rights reserved
